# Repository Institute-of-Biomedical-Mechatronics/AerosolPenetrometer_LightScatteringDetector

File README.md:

# AerosolPenetrometer_LightScatteringDetector
This repository contains all data for the aerosol penetrometer-light scattering detector like described in the research article:

Lifka S, Ponomarev I, Weth A et al. A simple and cheap aerosol penetrometer for filter testing using an electronic cigarette. [version 1; peer review: 1 approved with reservations]. Open Research Europe 2021, 1:5 (https://doi.org/10.12688/openreseurope.13087.1)

Contains the following underlying data:
- Underlying_Data.xlsx (Excel file containing the underlying data of the results presented in the figures)
- Statistical_analysis.py (Python file for all statistical analysis of the measurement results and figure generation)

Contains the following extended data:
- Aerosol_Penetrometer_Light_Scattering_Detector_V1
	- Holder.stp (CAD file for the holder of the setup)
	-Ambient_Light_Shielding.stp (CAD file of the ambient light shielding)
	- Measurement_Chamber.stp (CAD file of the measurement chambers)
	- Electronic_Cigarette_Adapter.stp (CAD file for the electronic cigarette adapter)
	- Aerosol_Penetrometer_Light_Scattering_Detector_Arduino.ino (Arduino program for the light 		  scattering detector)
	- Aerosol_Penetrometer_Light_Scattering_Detector.py (Python class file for the light scattering 		  detector)
	- Aerosol_Penetrometer_Light_Scattering_Detector_Measurement_Script.py (Python 			  measurement script for the light scattering detector)
	- Measurement_Principal.pdf (Illustration of the measurement principle)
	- Electronics.pdf (Electronic circuitry of the light scattering detector)
	- Setup.pdf (Illustration of the measurement setup)
	- Setup_Picture.pdf (Picture of the measurement setup)
	
- Aerosol_Penetrometer_Light_Scattering_Detector_V2:
	- Assembly.step (CAD file of the assembly)
	- Body.step (CAD file of the body)
	- Cover.step (CAD file of the cover)
	- Electronic_Cigarette.step (CAD-file of the electronic cigarette)
	- Filterholder.step (CAD file of the filter holder)
	- Measurement_Chamber_fixed.step (CAD file of the measurement chamber before the filter)
	- Measurement_Chamber.step (CAD file of the measurement chamber after the filter)
	- NanoV3.3.step (CAD file of the Arduino Nano board)
	- PCB_Assembly.step (CAD file of the PCB assembly)
	- PCB.step (CAD file of the PCB)
	- Syringe.step (CAD file of the syringe)
	- Aerosol_Penetrometer_Light_Scattering_Detector_V2.ino (Arduino program for the light 		  	 scattering detector)
	- Aerosol_Penetrometer_Light_Scattering_Detector_V2 (Python class file for the light scattering    	 detector)
	- Aerosol_Penetrometer_Light_Scattering_Detector_V2_Measurement_Script (Python 			  measurement script for the light scattering detector)
	- Penetrometer_V3_PCB.sch (Schematic file of the PCB)
	- Penetrometer_V3_PCB.brd (Board file of the PCB)

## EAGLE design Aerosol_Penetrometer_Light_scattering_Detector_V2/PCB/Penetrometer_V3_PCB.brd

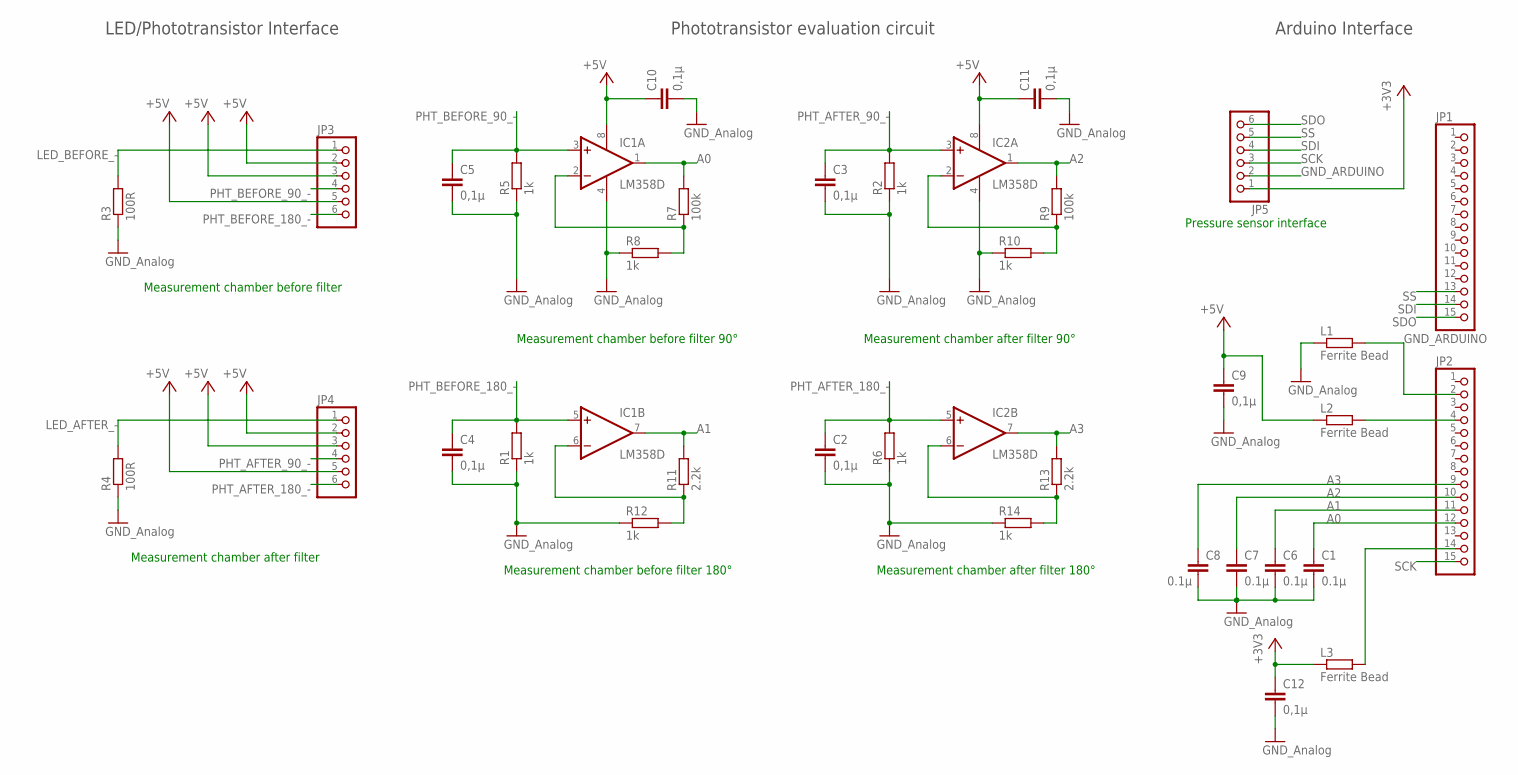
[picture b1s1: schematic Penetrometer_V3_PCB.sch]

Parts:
C1, C6, C7, C8: 0.1µ; C0603K
C2, C3, C4, C5, C9, C10, C11, C12: 0,1µ; C0603K
IC1, IC2: LM358D; SO08
JP1, JP2: PINHD-1X15; 1X15
JP3, JP4, JP5: PINHD-1X6; 1X06
L1, L2, L3: Ferrite Bead; R0603
R1, R2, R5, R6, R8, R10, R12, R14: 1k; R0603
R3, R4: 100R; R0603
R7, R9: 100k; R0603
R11, R13: 2.2k; R0603

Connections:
+3V3: C12.1, JP5.1, L3.1
+5V: C9.1, C10.1, C11.1, IC1.8 (V+), IC2.8 (V+), JP3.2, JP3.3, JP3.5, JP4.2, JP4.3, JP4.5, L2.1
A0: C1.1, IC1.1 (OUT), JP2.12, R7.2
A1: C6.1, IC1.7 (OUT), JP2.11, R11.2
A2: C7.1, IC2.1 (OUT), JP2.10, R9.2
A3: C8.1, IC2.7 (OUT), JP2.9, R13.2
GND: C1.2, C2.2, C3.2, C4.2, C5.2, C6.2, C7.2, C8.2, C9.2, C10.2, C11.2, C12.2, IC1.4 (V-), IC2.4 (V-), L1.1, R1.1, R2.1, R3.1, R4.1, R5.1, R6.1, R8.1, R10.1, R12.1, R14.1
GND_ARDUINO: JP2.2, JP5.2, L1.2
LED_AFTER_-: JP4.1, R4.2
LED_BEFORE_-: JP3.1, R3.2
unnamed: JP2.4, L2.2
unnamed: IC1.2 (-IN), R7.1, R8.2
unnamed: IC2.2 (-IN), R9.1, R10.2
unnamed: IC1.6 (-IN), R11.1, R12.2
unnamed: IC2.6 (-IN), R13.1, R14.2
unnamed: JP2.14, L3.2
PHT_AFTER_90_-: C3.1, IC2.3 (+IN), JP4.4, R2.2
PHT_AFTER_180_-: C2.1, IC2.5 (+IN), JP4.6, R6.2
PHT_BEFORE_90_-: C5.1, IC1.3 (+IN), JP3.4, R5.2
PHT_BEFORE_180_-: C4.1, IC1.5 (+IN), JP3.6, R1.2
SCK: JP2.15, JP5.3
SDI: JP1.14, JP5.4
SDO: JP1.15, JP5.6
SS: JP1.13, JP5.5

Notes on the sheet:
Measurement chamber before filter 180°
Measurement chamber before filter 90°
Measurement chamber after filter 180°
Measurement chamber after filter 90°
LED/Phototransistor Interface
Phototransistor evaluation circuit
Arduino Interface
Pressure sensor interface
Measurement chamber before filter
Measurement chamber after filter

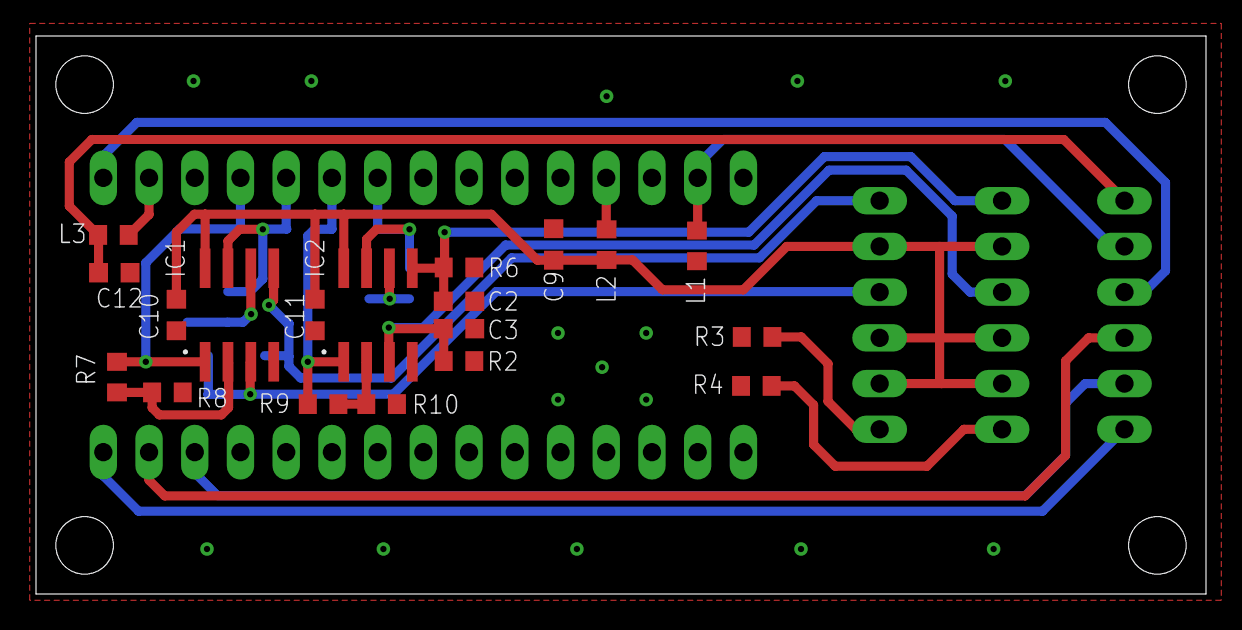
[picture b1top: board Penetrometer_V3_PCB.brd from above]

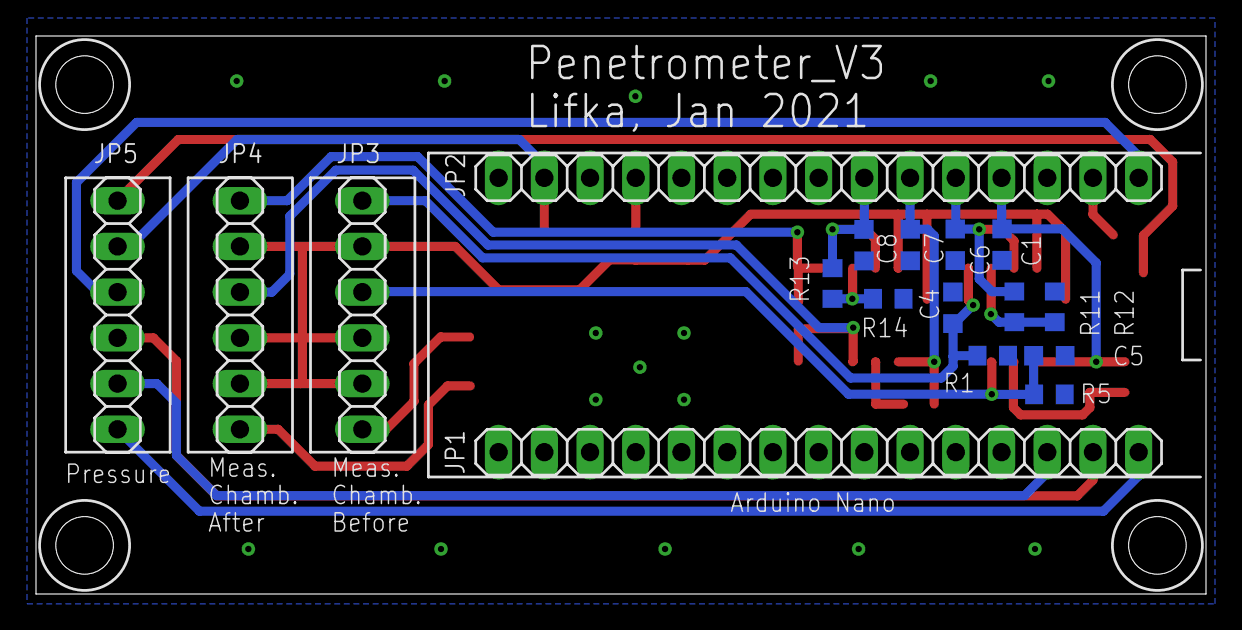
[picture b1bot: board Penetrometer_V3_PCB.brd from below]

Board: 2 copper layers, 65.0 x 31.0 mm, 36 parts (17 on the bottom side), 24 nets.

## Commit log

2020-12-10 Add files via upload
    Uploaded the class and the measurement script for the light scattering detector
2020-12-11 Add files via upload
    3D printable .stp files for the light scattering detector
2021-02-01 Update README.md
    Added DOI
2021-06-22 Added folder structure
2021-06-23 Added all files
2021-11-09 Changed function markFlowStartStop()
    Previous function did not work with Python 3.9
